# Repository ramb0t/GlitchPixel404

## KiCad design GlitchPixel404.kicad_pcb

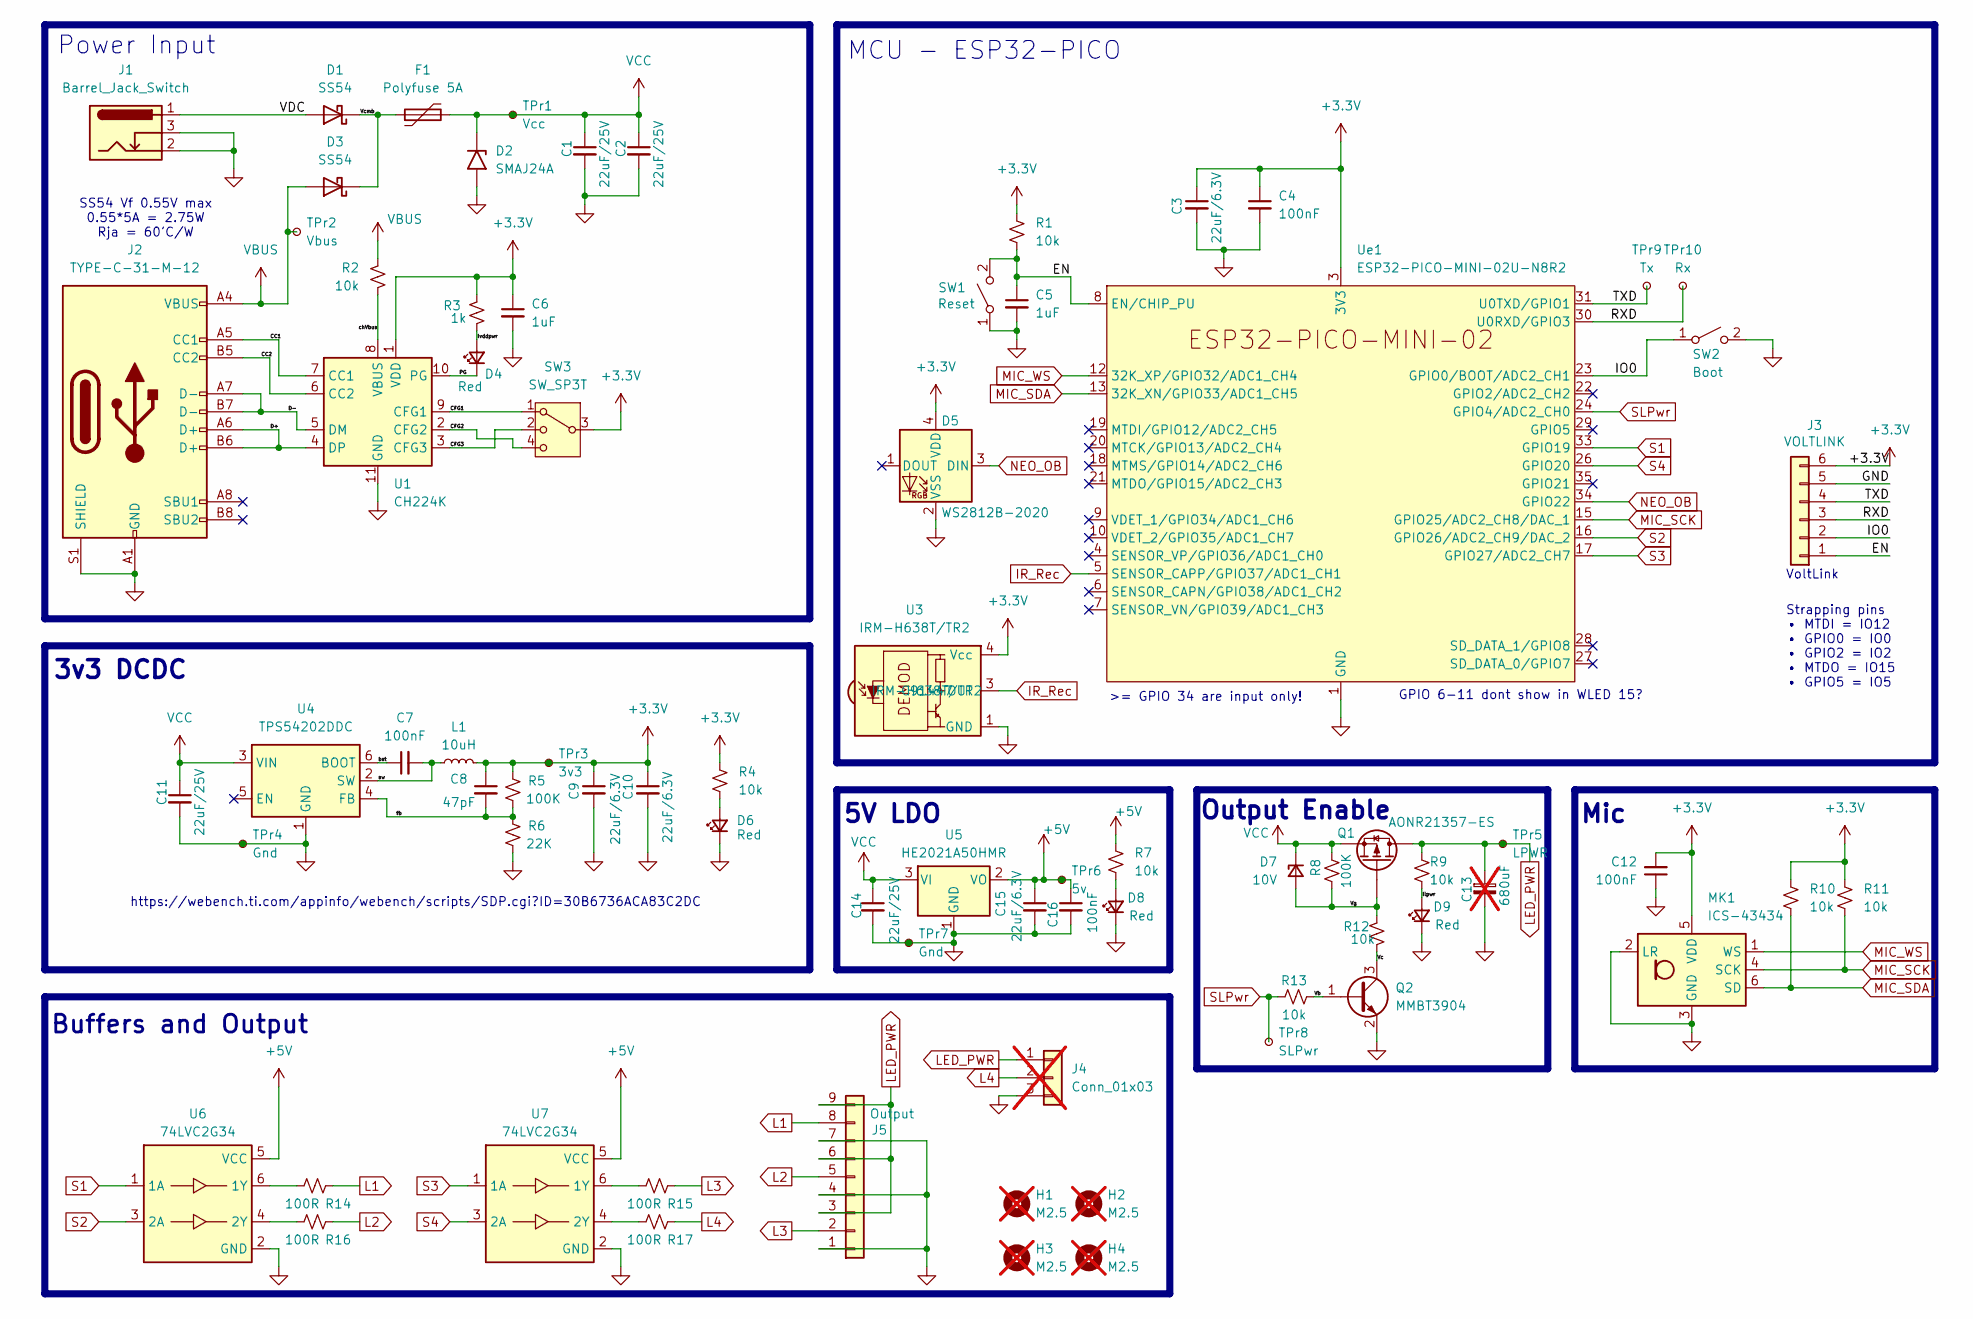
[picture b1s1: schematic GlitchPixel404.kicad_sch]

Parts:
C1, C2, C11, C14: 22uF/25V; C_0805_2012Metric; Voltage 25V; MPN CL21A226MAQNNNE; LCSC C45783
C3, C9, C10, C15: 22uF/6.3V; C_0603_1608Metric; MPN CL10A226MQ8NRNC; LCSC C59461
C4, C7, C12, C16: 100nF; C_0402_1005Metric; MPN CL05B104KO5NNNC; LCSC C1525
C5, C6: 1uF; C_0603_1608Metric; MPN CL10A105KB8NNNC; LCSC C15849
C8: 47pF; C_0402_1005Metric; MPN 0402CG470J500NT; LCSC C1567
C13: 680uF; CP_Elec_10x12.5; not fitted
D1, D3: SS54; D_SMA; MPN SS54; LCSC C22452
D2: SMAJ24A; D_SMA; LCSC C3001960
D4, D6: Red; LED_0603_1608Metric; MPN 19-213/Y2C-CQ2R2L/3T(CY); LCSC C2286
D5: WS2812B-2020; LED_WS2812B-2020_PLCC4_2.0x2.0mm; LCSC C965555
D7: 10V; D_SOD-123; MPN BZT52C10; LCSC C173431
D8, D9: Red; LED_0603_1608Metric; MPN 19-217/GHC-YR1S2/3T; LCSC C2286
F1: Polyfuse 5A; Fuse_2920_7451Metric; MPN BSMD2920-500-30V; LCSC C20539728
H1, H2, H3, H4: M2.5; MountingHole_2.7mm_M2.5_DIN965; not fitted
J1: Barrel_Jack_Switch; BarrelJack_Horizontal
J2: TYPE-C-31-M-12; USB_C_Receptacle_HRO_TYPE-C-31-M-12; MPN TYPE-C-31-M-12; LCSC C165948
J3: VOLTLINK; JST_SH_BM06B-SRSS-TB_1x06-1MP_P1.00mm_Vertical; MPN WTB01L06BA; LCSC C5120200
J4: Conn_01x03; PinHeader_1x03_P2.54mm_Vertical; not fitted
J5: Output; CONN-TH_9P-P2.54_MX128-2.54-09P-GN01-CU-Y-A; LCSC C5188449
L1: 10uH; L_Changjiang_FNR4018S; MPN FNR4018S100MT; LCSC C167808
MK1: ICS-43434; InvenSense_ICS-43434-6_3.5x2.65mm; LCSC C5656610
Q1: AONR21357-ES; DFN-8-1EP_3x3mm_P0.65mm_EP1.5x2.25mm; MPN AONR21357-ES; LCSC C22379638
Q2: MMBT3904; SOT-23; LCSC C20526
R1, R2, R4, R7, R9, R10, R11, R13: 10k; R_0402_1005Metric; MPN 0402WGF1002TCE; LCSC C25744
R3: 1k; R_0402_1005Metric; MPN 0402WGF1001TCE; LCSC C11702
R5, R8: 100K; R_0402_1005Metric; MPN 0402WGF1003TCE; LCSC C25741
R6: 22K; R_0402_1005Metric; MPN 0402WGF2202TCE; LCSC C25768
R12: 10k; R_0402_1005Metric; MPN 0402WGF1001TCE; LCSC C25744
R14, R15, R16, R17: 100R; R_0603_1608Metric; MPN 0603WAF1000T5E; LCSC C22775
SW1: Reset; SW_Push_SPST_NO_Alps_SKRK; MPN TS342A2P-WZ; LCSC C557591
SW2: Boot; SW_Push_SPST_NO_Alps_SKRK; MPN TS342A2P-WZ; LCSC C557591
SW3: SW_SP3T; SW_SP3T_PCM13; MPN MSK13C02-BB 125; LCSC C2858293
TPr1: Vcc; TestPoint_Pad_D1.0mm
TPr2: Vbus; TestPoint_Pad_D1.0mm
TPr3: 3v3; TestPoint_Pad_D1.0mm
TPr4, TPr7: Gnd; TestPoint_Pad_D1.0mm
TPr5: LPWR; TestPoint_Pad_D1.0mm
TPr6: 5v; TestPoint_Pad_D1.0mm
TPr8: SLPwr; TestPoint_Pad_D1.0mm
TPr9: Tx; TestPoint_Pad_D1.0mm
TPr10: Rx; TestPoint_Pad_D1.0mm
U1: CH224K; SSOP-10-1EP_3.9x4.9mm_P1mm_EP2.1x3.3mm; LCSC C970725
U3: IRM-H638T/TR2; Everlight_IRM-H6xxT; MPN IRM-H638T/TR2; LCSC C91447
U4: TPS54202DDC; SOT-23-6; LCSC C191884
U5: HE2021A50HMR; SOT-23; LCSC C711948
U6, U7: 74LVC2G34; SOT-363_SC-70-6; MPN SN74LVC2G34DCKR; LCSC C14461
Ue1: ESP32-PICO-MINI-02U-N8R2; ESP32-PICO-MINI-02; LCSC C2980306

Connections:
+3.3V: C3.1, C4.1, C6.1, C8.1, C9.1, C10.1, C12.2, D5.4 (VDD), J3.6, L1.2, MK1.5 (VDD), R1.1, R3.2, R4.1, R5.1, R10.1, R11.1, SW3.3, TPr3.1, U1.1 (VDD), U3.4 (Vcc), Ue1.3 (3V3)
+5V: C15.1, C16.1, R7.1, TPr6.1, U5.2 (VO), U6.5 (VCC), U7.5 (VCC)
/CC1: J2.A5 (CC1), U1.7 (CC1)
/CC2: J2.B5 (CC2), U1.6 (CC2)
/CFG1: SW3.1, U1.9 (CFG1)
/CFG2: SW3.4, U1.2 (CFG2)
/CFG3: SW3.2, U1.3 (CFG3)
/D+: J2.A6 (D+), J2.B6 (D+), U1.4 (DP)
/D-: J2.A7 (D-), J2.B7 (D-), U1.5 (DM)
/EN: C5.1, J3.1, R1.2, SW1.2 (B), Ue1.8 (EN/CHIP_PU)
/IO0: J3.2, SW2.1 (A), Ue1.23 (GPIO0/BOOT/ADC2_CH1)
/PG: D4.1 (K), U1.10 (PG)
/RXD: J3.3, TPr10.1, Ue1.30 (U0RXD/GPIO3)
/TXD: J3.4, TPr9.1, Ue1.31 (U0TXD/GPIO1)
/VDC: D1.2 (A), J1.1
/Vb: Q2.1 (B), R13.2
/Vc: Q2.3 (C), R12.1
/Vcmb: D1.1 (K), D3.1 (K), F1.1
/Vg: D7.2 (A), Q1.G, R8.1, R12.2
/bst: C7.1, U4.6 (BOOT)
/chVbus: R2.2, U1.8 (VBUS)
/fb: C8.2, R5.2, R6.1, U4.4 (FB)
/llpwr: D9.2 (A), R9.2
/lvddpwr: D4.2 (A), R3.1
/sw: C7.2, L1.1, U4.2 (SW)
GND: C1.2, C2.2, C3.2, C4.2, C5.2, C6.2, C9.2, C10.2, C11.2, C12.1, C13.2, C14.2, C15.2, C16.2, D2.2 (A2), D5.2 (VSS), D6.1 (K), D8.1 (K), D9.1 (K), J1.2, J1.3, J2.A1 (GND), J2.A12 (GND), J2.B1 (GND), J2.B12 (GND), J2.S1 (SHIELD), J3.5, J4.3, J5.1, J5.4, J5.7, MK1.2 (LR), MK1.3 (GND), Q2.2 (E), R6.2, SW1.1 (A), SW2.2 (B), TPr4.1, TPr7.1, U1.11 (GND), U3.1 (GND), U3.2 (GND), U4.1 (GND), U5.1 (GND), U6.2 (GND), U7.2 (GND), Ue1.1 (GND), Ue1.2 (GND), Ue1.11 (GND), Ue1.14 (GND), Ue1.36 (GND), Ue1.37 (GND), Ue1.38 (GND), Ue1.39 (GND), Ue1.40 (GND), Ue1.41 (GND), Ue1.42 (GND), Ue1.43 (GND), Ue1.44 (GND), Ue1.45 (GND), Ue1.46 (GND), Ue1.47 (GND), Ue1.48 (GND), Ue1.49 (GND), Ue1.50 (GND), Ue1.51 (GND), Ue1.52 (GND), Ue1.53 (GND)
IR_Rec: U3.3 (OUT), Ue1.5 (SENSOR_CAPP/GPIO37/ADC1_CH1)
L1: J5.8, R14.1
L2: J5.5, R16.1
L3: J5.2, R15.1
L4: J4.2, R17.1
LED_PWR: C13.1, J4.1, J5.3, J5.6, J5.9, Q1.D, R9.1, TPr5.1
MIC_SCK: MK1.4 (SCK), R11.2, Ue1.15 (GPIO25/ADC2_CH8/DAC_1)
MIC_SDA: MK1.6 (SD), R10.2, Ue1.13 (32K_XN/GPIO33/ADC1_CH5)
MIC_WS: MK1.1 (WS), Ue1.12 (32K_XP/GPIO32/ADC1_CH4)
NEO_OB: D5.3 (DIN), Ue1.34 (GPIO22)
unnamed: D6.2 (A), R4.2
unnamed: D8.2 (A), R7.2
unnamed: R14.2, U6.6 (1Y)
unnamed: R16.2, U6.4 (2Y)
unnamed: R15.2, U7.6 (1Y)
unnamed: R17.2, U7.4 (2Y)
S1: U6.1 (1A), Ue1.33 (GPIO19)
S2: U6.3 (2A), Ue1.16 (GPIO26/ADC2_CH9/DAC_2)
S3: U7.1 (1A), Ue1.17 (GPIO27/ADC2_CH7)
S4: U7.3 (2A), Ue1.26 (GPIO20)
SLPwr: R13.1, TPr8.1, Ue1.24 (GPIO4/ADC2_CH0)
VBUS: D3.2 (A), J2.A4 (VBUS), J2.A9 (VBUS), J2.B4 (VBUS), J2.B9 (VBUS), R2.1, TPr2.1
VCC: C1.1, C2.1, C11.1, C14.1, D2.1 (A1), D7.1 (K), F1.2, Q1.S, R8.2, TPr1.1, U4.3 (VIN), U5.3 (VI)

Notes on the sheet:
3v3 DCDC
Mic
Output Enable
MCU - ESP32-PICO
https://webench.ti.com/appinfo/webench/scripts/SDP.cgi?ID=30B6736ACA83C2DC
Strapping pins • MTDI = IO12 • GPIO0 = IO0 • GPIO2 = IO2 • MTDO = IO15 • GPIO5 = IO5
Power Input
>= GPIO 34 are input only!
Buffers and Output
GPIO 6-11 dont show in WLED 15?
5V LDO
VoltLink
SS54 Vf 0.55V max 0.55*5A = 2.75W Rja = 60'C/W

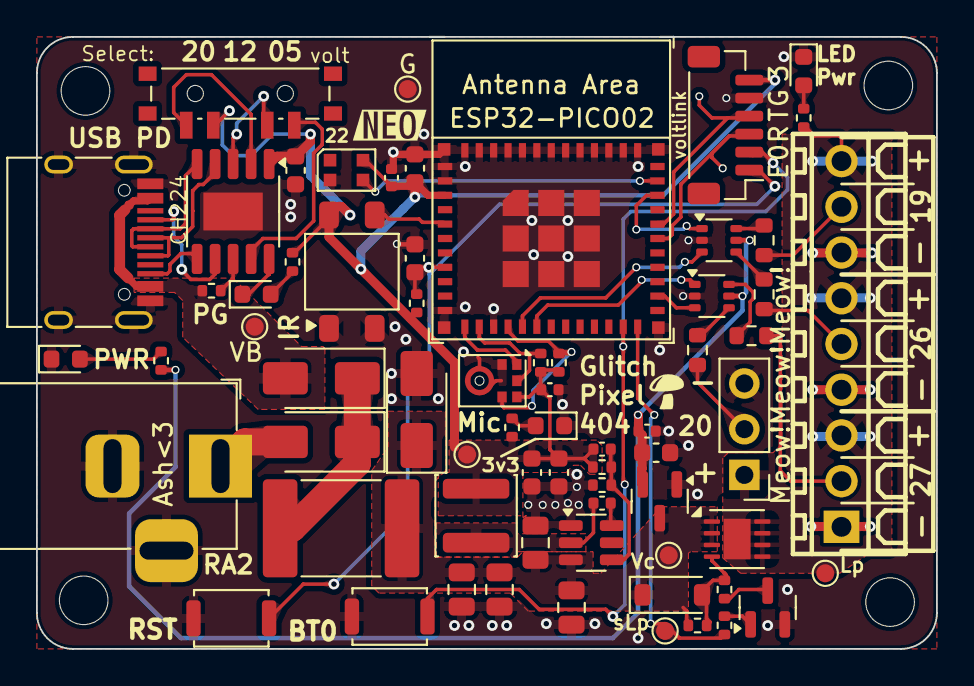
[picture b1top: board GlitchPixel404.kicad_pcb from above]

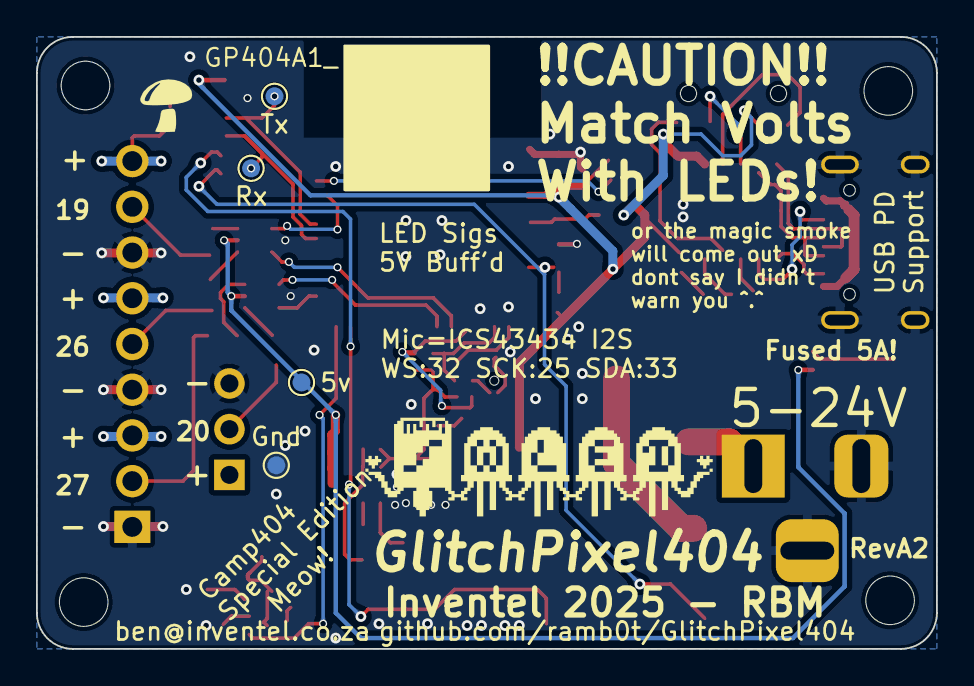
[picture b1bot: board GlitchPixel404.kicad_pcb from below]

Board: 2 copper layers, 50.0 x 34.0 mm, 76 parts (4 on the bottom side), 49 nets.

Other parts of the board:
kibuzzard-67E14B7B: G***; kibuzzard-67E14B7B

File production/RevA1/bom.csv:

Designator,Footprint,Quantity,Value,LCSC Part #
"C1, C11, C14, C2",0805,4,22uF/25V,C45783
"C10, C15, C3, C9",0603,4,22uF/6.3V,C59461
"C12, C16, C4, C7",0402,4,100nF,C1525
"C5, C6",0603,2,1uF,C15849
C8,0402,1,47pF,C1567
"D1, D3",D_SMA,2,SS54,C22452
D2,D_SMA,1,SMAJ24A,C3001960
"D4, D6, D8, D9",0603,4,Red,C2286
D5,LED_WS2812B-2020_PLCC4_2.0x2.0mm,1,WS2812B-2020,C965555
D7,D_SOD-123,1,10V,C173431
F1,2920,1,Polyfuse 5A,C20539728
J2,USB_C_Receptacle_HRO_TYPE-C-31-M-12,1,USB_C_Receptacle_USB2.0_16P,C165948
J3,JST_SH_BM06B-SRSS-TB_1x06-1MP_P1.00mm_Vertical,1,VOLTLINK,C5120200
L1,L_Changjiang_FNR4018S,1,10uH,C167808
MK1,InvenSense_ICS-43434-6_3.5x2.65mm,1,ICS-43434,C5656610
Q1,DFN-8-1EP_3x3mm_P0.65mm_EP1.5x2.25mm,1,AONR21357-ES,C22379638
Q2,SOT-23,1,MMBT3904,C20526
"R1, R10, R11, R13, R2, R4, R7, R9",0402,8,10k,C25744
"R12, R3",0402,2,1k,C11702
"R14, R15, R16, R17",0603,4,100R,C22775
"R5, R8",0402,2,100K,C25741
R6,0402,1,22K,C25768
SW1,SW_Push_SPST_NO_Alps_SKRK,1,Reset,
SW2,SW_Push_SPST_NO_Alps_SKRK,1,Boot,
SW3,SW_SP3T_PCM13,1,SW_SP3T,C2858293
U1,SSOP-10-1EP_3.9x4.9mm_P1mm_EP2.1x3.3mm,1,CH224K,C970725
U2,ESP32-PICO-MINI-02,1,ESP32-PICO-MINI-02U-N8R2,C2980306
U3,Everlight_IRM-H6xxT,1,IRM-H638T/TR2,C91447
U4,SOT-23-6,1,TPS54202DDC,C191884
U5,SOT-23,1,HE2021A50HMR,C711948
"U6, U7",SOT-363_SC-70-6,2,74LVC2G34,C14461

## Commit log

2025-03-15 Add USB PD Trig Circuit
2025-03-17 Changed buffers to 74LVC2G34 and added datasheets
2025-03-17 Added 3v3 DCDC
2025-03-17 Parts selection and 0402
2025-03-17 Update README with latest changes
2025-03-18 Added fet protection and started layout
2025-03-23 remove CH340 and start layout
2025-03-24 Layout 80% complete, some circuit changes
2025-03-24 Minor corrections, silk started
2025-03-24 Adjusted component selection
    Final silk and checks before prototype batch ready
2025-03-24 RevA1
    Sent for manufacture of prototypes
2025-04-09 Add Drawings and 3D Files
2025-04-11 Case Design Complete
2025-07-17 Started A2 HW Rev, Fixed R12
2026-04-19 Add schematic pdf
2026-04-20 Update silkscreen
